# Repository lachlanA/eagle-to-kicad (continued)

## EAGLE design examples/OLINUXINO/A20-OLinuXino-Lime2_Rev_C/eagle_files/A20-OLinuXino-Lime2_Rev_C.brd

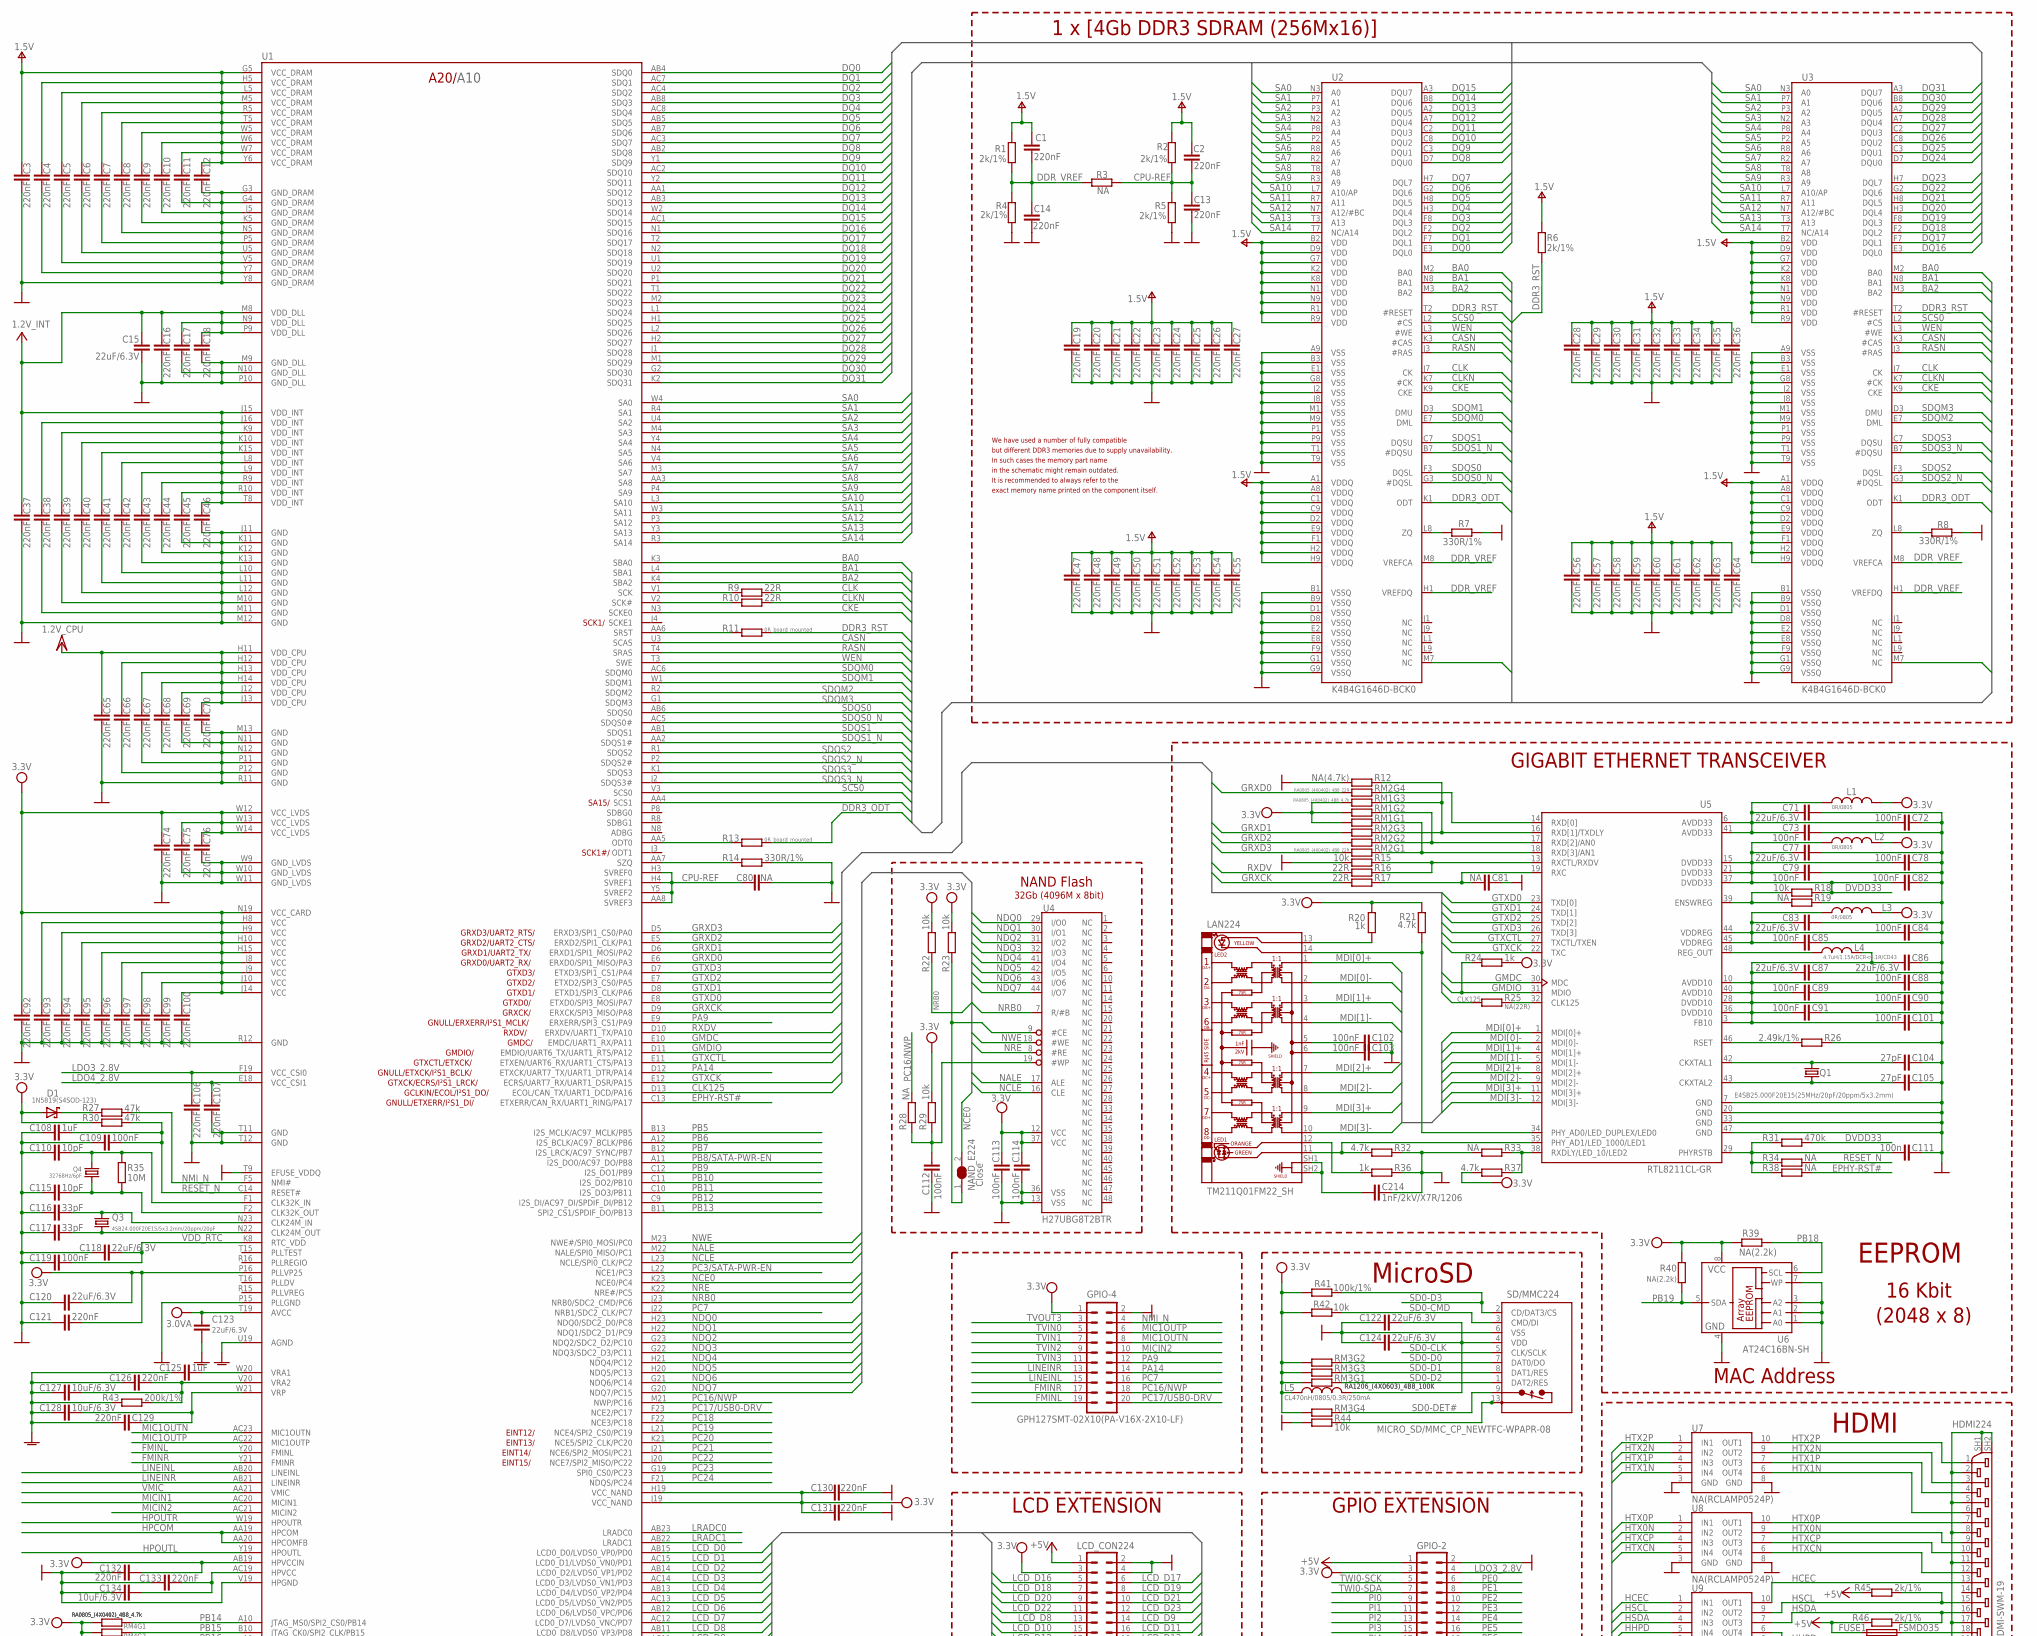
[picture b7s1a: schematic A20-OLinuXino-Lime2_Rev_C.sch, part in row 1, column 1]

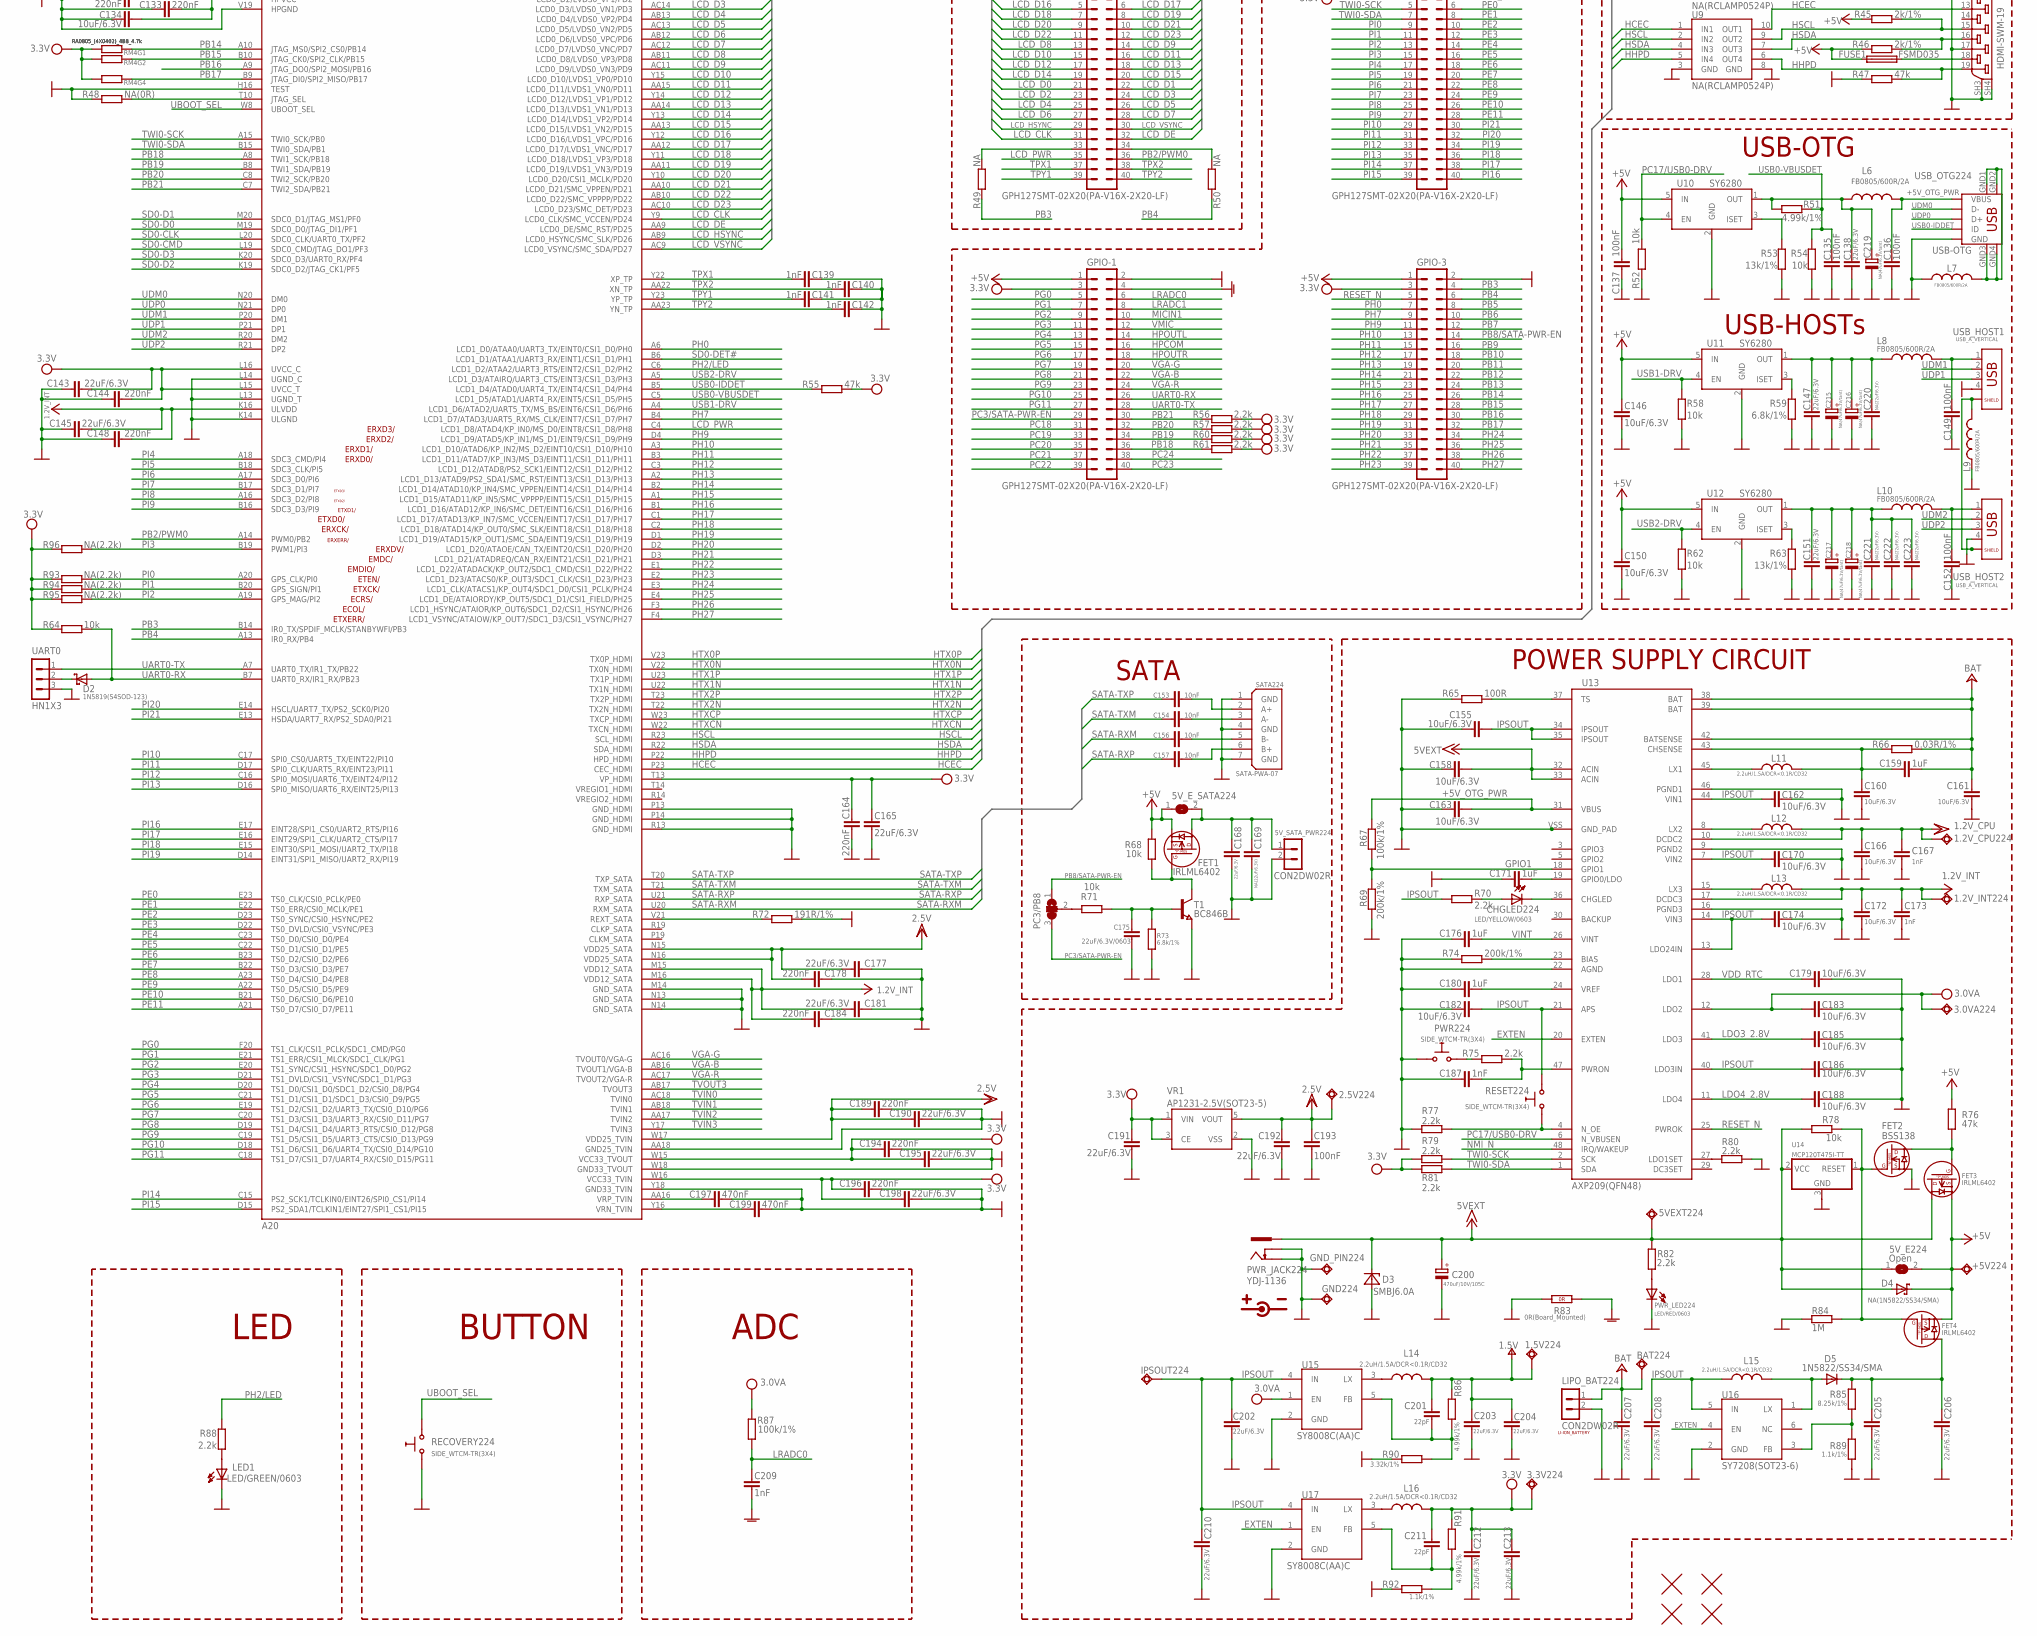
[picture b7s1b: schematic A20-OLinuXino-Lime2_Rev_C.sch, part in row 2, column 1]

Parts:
1.2V_CPU224, 1.2V_INT224, 1.5V224, 2.5V224, 3.0VA224, 3.3V224, 5VEXT224: TESTPADTESTPAD_40-ROUND; TESTPAD_40-ROUND
5V_E224: Open; SJ_1_SMALLER
5V_E_SATA224: SJSJ_SMALLER; SJ_1_SMALLER
5V_SATA_PWR224: CON2DW02R; DW02R
+5V224: TESTPADTESTPAD_40-ROUND; TESTPAD_40-ROUND
BAT224: TESTPADTESTPAD_40-ROUND; TESTPAD_40-ROUND
C1, C2, C3, C4, C5, C6, C7, C8, C9, C10, C11, C12, C13, C14, C16, C17, C18, C19, C20, C21, C22, C23, C24, C25, C26, C27, C28, C29, C30, C31, C32, C33, C34, C35, C36, C37, C38, C39, C40, C41, C42, C43, C44, C45, C46, C47, C48, C49, C50, C51, C52, C53, C54, C55, C56, C57, C58, C59, C60, C61, C62, C63, C64, C65, C66, C67, C68, C69, C70, C74, C75, C76, C92, C93, C94, C95, C96, C97, C98, C99, C100, C106, C107, C121, C126, C129, C130, C131, C132, C133, C144, C148, C164, C178, C184, C189, C194, C196: 220nF; C0402_TI
C15, C71, C77, C83, C86, C87, C118, C120, C122, C123, C124, C138, C143, C145, C147, C151, C165, C168, C177, C181, C190, C191, C192, C195, C198, C202, C203, C204, C205, C206, C207, C208, C210, C212, C213: 22uF/6.3V; C0603_DWS
C72, C73, C78, C79, C82, C84, C85, C88, C89, C90, C91, C101, C102, C103, C109, C112, C113, C114, C119, C135, C136, C137, C149, C152, C193: 100nF; C0402_TI
C80, C81: NA; C0402_TI
C104, C105: 27pF; C0603_DWS
C108, C125, C159, C171, C176, C180: 1uF; C0603_DWS
C110, C115: 10pF; C0402_TI
C111: 100n; C0402_TI
C116, C117: 33pF; C0603_DWS
C127, C128, C134, C146, C150, C155, C158, C160, C161, C162, C163, C166, C170, C172, C174, C179, C182, C183, C185, C186, C188: 10uF/6.3V; C0603_DWS
C139, C140, C141, C142, C167, C173, C187, C209: 1nF; C0402_TI
C153, C154, C156, C157: 10nF; C0402_TI
C169, C220, C221, C222, C223: NA(22uF/6.3V); C0603_DWS
C175: 22uF/6.3V/0603; C0603_DWS
C197, C199: 470nF; C0603_DWS
C200: 470uF/10V/105C; E2,5-6,3
C201, C211: 22pF; C0603_DWS
C214: 1nF/2kV/X7R/1206; C1206_5MILS_WS_ISO
C215, C216, C217, C218, C219: NA(47uF/6.3V/tant); CT3528_MIL
CHGLED224: LED/YELLOW/0603; LED-0603
D1, D2: 1N5819(S4SOD-123); SOD-123
D3: SMBJ6.0A; DO214AA
D4: NA(1N5822/SS34/SMA); MLL-41
D5: 1N5822/SS34/SMA; MELF-MLL41
FET1, FET3, FET4: IRLML6402; SOT23
FET2: BSS138; SOT23
FUSE1: FSMD035; 1206
GND224: TESTPADTESTPAD_40-ROUND; TESTPAD_40-ROUND
GND_PIN224: TESTPAD3; TEST_PAD40/70/SQUARE
GPIO-1, GPIO-2, GPIO-3: GPH127SMT-02X20(PA-V16X-2X20-LF)
GPIO-4: GPH127SMT-02X10(PA-V16X-2X10-LF)
HDMI224: HDMI-SWM-19
IPSOUT224: TESTPADTESTPAD_40-ROUND; TESTPAD_40-ROUND
L1, L2, L3: 0R/0805; L0805_5MIL_DWS
L4: 4.7uH/1.15A/DCR<0.1R/CD43; CD42(43)
L5: CL470nH/0805/0.3R/250mA; L0805_5MIL_DWS
L6, L7, L8, L9, L10: FB0805/600R/2A; L0805_5MIL_DWS
L11, L12, L13, L14, L15, L16: 2.2uH/1.5A/DCR<0.1R/CD32; CD32
LAN224: TM211Q01FM22_SH
LCD_CON224: GPH127SMT-02X20(PA-V16X-2X20-LF)
LED1: LED/GREEN/0603; LED-0603
LIPO_BAT224: CON2DW02R; DW02R
NAND_E224: Close; SJ_1_SMALLER_CLOSE_10MILS
PC3/PB8: SJ2W5; SJ_2_SMALL_23_TIED
PWR224: SIDE_WTCM-TR(3X4); SW_TAKT3X4
PWR_JACK224: YDJ-1136; PWR_JACK_UNI_MILLING
PWR_LED224: LED/RED/0603; LED-0603
Q1: E4SB25.000F20E15(25MHz/20pF/20ppm/5x3.2mm); HCX-4S
Q3: 4SB24.000F20E15/5x3.2mm/20ppm/20pF; HCX-4S
Q4: 32768Hz/6pF; MC-306
R1, R2, R4, R5, R6, R45, R46: 2k/1%; R0402_TI
R3, R19, R28, R33, R34, R38: NA; R0402_TI
R7, R8, R14: 330R/1%; R0603_5MIL_DWS
R9, R10, R16, R17: 22R; R0402_TI
R11, R13: 0R_board_mounted; R0402_TI_0R
R12: NA(4.7k); R0402_TI
R15, R18, R22, R23, R29, R42, R44, R52, R54, R58, R62, R64, R68, R71, R78: 10k; R0402_TI
R20, R24, R36: 1k; R0402_TI
R21, R32, R37: 4.7k; R0402_TI
R25: NA(22R); R0402_TI
R26: 2.49k/1%; R0603_5MIL_DWS
R27, R30, R47, R55, R76: 47k; R0402_TI
R31: 470k; R0402_TI
R35: 10M; R0402_TI
R39, R40, R93, R94, R95, R96: NA(2.2k); R0402_TI
R41, R67, R87: 100k/1%; R0603_5MIL_DWS
R43, R69, R74: 200k/1%; R0603_5MIL_DWS
R48: NA(0R); R0603_5MIL_DWS
R49, R50: NA; R0603_5MIL_DWS
R51, R86, R91: 4.99k/1%; R0603_5MIL_DWS
R53, R63: 13k/1%; R0603_5MIL_DWS
R56, R57, R60, R61, R70, R75, R77, R79, R80, R81, R82, R88: 2.2k; R0402_TI
R59, R73: 6.8k/1%; R0603_5MIL_DWS
R65: 100R; R0603_5MIL_DWS
R66: 0.03R/1%; R1206_5MIL_WS
R72: 191R/1%; R0603_5MIL_DWS
R83: 0R(Board_Mounted); 0603_0R
R84: 1M; R0402_TI
R85: 8.25k/1%; R0603_5MIL_DWS
R89, R92: 1.1k/1%; R0603_5MIL_DWS
R90: 3.32k/1%; R0603_5MIL_DWS
RECOVERY224: SIDE_WTCM-TR(3X4); SW_TAKT3X4
RESET224: SIDE_WTCM-TR(3X4); SW_TAKT3X4
RM1, RM4: RA0805_(4X0402)_4B8_4.7k; R_MATRIX_4_0402_25X625
RM2: RA0805_(4X0402)_4B8_22R; R_MATRIX_4_0402_25X625
RM3: RA1206_(4X0603)_4B8_100K; R_MATRIX_4
SATA224: SATA-PWA-07
SD/MMC224: MICRO_SD/MMC_CP_NEWTFC-WPAPR-08; TFC-WPAPR-08
T1: BC846B; SOT23
U1: A20; TFBGA441
U2, U3: K4B4G1646D-BCK0; FBGA96_SK
U4: H27UBG8T2BTR; TSOP48
U5: RTL8211CL-GR; LQFP48
U6: AT24C16BN-SH; SO-08MN
U7, U8, U9: NA(RCLAMP0524P); SLP2510P8
U10, U11, U12: SY6280; SOT23-5
U13: AXP209(QFN48); QFN48
U14: MCP120T475I-TT; SOT23
U15, U17: SY8008C(AA)C; SOT23-5
U16: SY7208(SOT23-6); SOT23-6
U18, U19, U20, U21: FIDUCIAL; FIDUCIAL-1X3
UART0: HN1X3
USB_HOST1, USB_HOST2: USB_A_VERTICAL; USB_A_VERTICAL_PTH
USB_OTG224: USB-OTG; USB_MINI_9PIN
VR1: AP1231-2.5V(SOT23-5); SOT-23-5

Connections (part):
5VEXT: 5VEXT224.1, 5V_E224.1, C158.2, C200.+, D3.C, D4.A, FET3.3 (D), PWR_JACK224.+, R78.1, R82.1, U13.32 (ACIN), U13.33 (ACIN), U14.2 (VCC)
+5V: 5V_E224.2, 5V_E_SATA224.1, +5V224.1, C137.1, C146.1, C150.1, D4.K (C), FET1.2 (S), FET3.2 (S), FET4.2 (S), FUSE1.1, GPIO-1.1, GPIO-2.1, GPIO-3.1, LCD_CON224.1, R45.2, R46.2, R68.1, R76.2, U10.5 (IN), U11.5 (IN), U12.5 (IN)
+5V_OTG_PWR: C136.1, C163.2, L6.1, R67.1, U13.31 (VBUS), USB_OTG224.VBUS
+24V: BAT224.1, C159.2, C161.1, C207.2, LIPO_BAT224.1, R66.2, U13.38 (BAT), U13.39 (BAT), U13.42 (BATSENSE)
AVDD1: C71.2, C72.2, C73.2, L1.2, U5.6 (AVDD33), U5.41 (AVDD33)
AVDD/DVDD(1.05V): C86.2, C87.2, C88.2, C89.2, C90.2, C91.2, C101.2, L4.2, U5.3 (FB10), U5.10 (AVDD10), U5.28 (DVDD10), U5.36 (DVDD10), U5.40 (AVDD10)
BA0: U1.K3 (SBA0), U2.M2 (BA0), U3.M2 (BA0)
BA1: U1.L4 (SBA1), U2.N8 (BA1), U3.N8 (BA1)
BA2: U1.K4 (SBA2), U2.M3 (BA2), U3.M3 (BA2)
CASN: U1.U3 (SCAS), U2.K3 (#CAS), U3.K3 (#CAS)
CKE: U1.N3 (SCKE0), U2.K9 (CKE), U3.K9 (CKE)
CLK: R9.1, U2.J7 (CK), U3.J7 (CK)
CLK125: R25.1, U1.D13 (ECOL/CAN_TX/UART1_DCD/PA16)
CLKN: R10.1, U2.K7 (#CK), U3.K7 (#CK)
CPU-REF: C2.2, C13.2, C80.2, R2.1, R3.2, R5.2, U1.AA8 (SVREF3), U1.H3 (SVREF0), U1.H4 (SVREF1), U1.Y5 (SVREF2)
DDR3_ODT: R13.1, U2.K1 (ODT), U3.K1 (ODT)
DDR3_RST: R6.1, R11.1, U2.T2 (#RESET), U3.T2 (#RESET)
DDR_VREF: C1.2, C14.2, R1.1, R3.1, R4.2, U2.H1 (VREFDQ), U2.M8 (VREFCA), U3.H1 (VREFDQ), U3.M8 (VREFCA)
DQ0: U1.AB4 (SDQ0), U2.E3 (DQL0)
DQ1: U1.AC7 (SDQ1), U2.F7 (DQL1)
DQ2: U1.AC4 (SDQ2), U2.F2 (DQL2)
DQ3: U1.AB8 (SDQ3), U2.F8 (DQL3)
DQ4: U1.AC8 (SDQ4), U2.H3 (DQL4)
DQ5: U1.AB5 (SDQ5), U2.H8 (DQL5)
DQ6: U1.AB7 (SDQ6), U2.G2 (DQL6)
DQ7: U1.AC3 (SDQ7), U2.H7 (DQL7)
DQ8: U1.AB2 (SDQ8), U2.D7 (DQU0)
DQ9: U1.Y1 (SDQ9), U2.C3 (DQU1)
DQ10: U1.AC2 (SDQ10), U2.C8 (DQU2)
DQ11: U1.Y2 (SDQ11), U2.C2 (DQU3)
DQ12: U1.AA1 (SDQ12), U2.A7 (DQU4)
DQ13: U1.AB3 (SDQ13), U2.A2 (DQU5)
DQ14: U1.W2 (SDQ14), U2.B8 (DQU6)
DQ15: U1.AC1 (SDQ15), U2.A3 (DQU7)
DQ16: U1.N1 (SDQ16), U3.E3 (DQL0)
DQ17: U1.T2 (SDQ17), U3.F7 (DQL1)
DQ18: U1.N2 (SDQ18), U3.F2 (DQL2)
DQ19: U1.U1 (SDQ19), U3.F8 (DQL3)
DQ20: U1.U2 (SDQ20), U3.H3 (DQL4)
DQ21: U1.P1 (SDQ21), U3.H8 (DQL5)
DQ22: U1.T1 (SDQ22), U3.G2 (DQL6)
DQ23: U1.M2 (SDQ23), U3.H7 (DQL7)
DQ24: U1.L1 (SDQ24), U3.D7 (DQU0)
DQ25: U1.H1 (SDQ25), U3.C3 (DQU1)
DQ26: U1.L2 (SDQ26), U3.C8 (DQU2)
DQ27: U1.H2 (SDQ27), U3.C2 (DQU3)
DQ28: U1.J1 (SDQ28), U3.A7 (DQU4)
DQ29: U1.M1 (SDQ29), U3.A2 (DQU5)
DQ30: U1.G2 (SDQ30), U3.B8 (DQU6)
DQ31: U1.K2 (SDQ31), U3.A3 (DQU7)
DVDD33: C77.2, C78.2, C79.2, C82.2, L2.2, R18.1, R31.1, U5.15 (DVDD33), U5.21 (DVDD33), U5.37 (DVDD33)
EPHY-RST#: R38.1, U1.C13 (ETXERR/CAN_RX/UART1_RING/PA17)
EXTEN: U13.20 (EXTEN), U16.4 (EN), U17.1 (EN)
FMINL: GPIO-4.19, U1.Y20 (FMINL)
FMINR: GPIO-4.17, U1.Y21 (FMINR)
GMDC: U1.E10 (EMDC/UART1_RX/PA11), U5.30 (MDC)
GMDIO: R24.1, U1.D11 (EMDIO/UART6_TX/UART1_RTS/PA12), U5.31 (MDIO)
GND: 5V_SATA_PWR224.2, C3.1, C4.1, C5.1, C6.1, C7.1, C8.1, C9.1, C10.1, C11.1, C12.1, C13.1, C14.1, C15.1, C16.1, C17.1, C18.1, C19.1, C20.1, C21.1, C22.1, C23.1, C24.1, C25.1, C26.1, C27.1, C28.1, C29.1, C30.1, C31.1, C32.1, C33.1, C34.1, C35.1, C36.1, C37.1, C38.1, C39.1, C40.1, C41.1, C42.1, C43.1, C44.1, C45.1, C46.1, C47.1, C48.1, C49.1, C50.1, C51.1, C52.1, C53.1, C54.1, C55.1, C56.1, C57.1, C58.1, C59.1, C60.1, C61.1, C62.1, C63.1, C64.1, C65.1, C66.1, C67.1, C68.1, C69.1, C70.1, C71.1, C72.1, C73.1, C74.1, C75.1, C76.1, C77.1, C78.1, C79.1, C80.1, C81.2, C82.1, C83.1, C84.1, C85.1, C86.1, C87.1, C88.1, C89.1, C90.1, C91.1, C92.1, C93.1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
GNDA: C123.1, C125.1, C126.1, C127.1, C128.1, C129.1, C209.2, GPIO-1.4, R43.2, R83.2 (1.2), U1.U19 (AGND)
GPIO1: R67.2, R69.1, U13.18 (GPIO1)
GRXCK: R17.2, U1.D9 (ERXCK/SPI3_MISO/PA8)
GRXD0: RM2.4.2 (2), U1.E6 (ERXD0/SPI1_MISO/PA3)
GRXD1: RM2.3.2 (2), U1.D6 (ERXD1/SPI1_MOSI/PA2)
GRXD2: RM2.2.2 (2), U1.E5 (ERXD2/SPI1_CLK/PA1)
GRXD3: RM2.1.2 (2), U1.D5 (ERXD3/SPI1_CS0/PA0)
GTXCK: U1.E12 (ECRS/UART7_RX/UART1_DSR/PA15), U5.22 (TXC)
GTXCTL: U1.E11 (ETXEN/UART6_RX/UART1_CTS/PA13), U5.27 (TXCTL/TXEN)
GTXD0: U1.E8 (ETXD0/SPI3_MOSI/PA7), U5.23 (TXD[0])
GTXD1: U1.D8 (ETXD1/SPI3_CLK/PA6), U5.24 (TXD[1])
GTXD2: U1.E7 (ETXD2/SPI3_CS0/PA5), U5.25 (TXD[2])
GTXD3: U1.D7 (ETXD3/SPI1_CS1/PA4), U5.26 (TXD[3])
HCEC: HDMI224.13, U1.P23 (CEC_HDMI), U9.1 (IN1), U9.10 (OUT1)
HDMI_5V_SOURCE: FUSE1.2, HDMI224.18
HHPD: HDMI224.19, R47.1, U1.P22 (HPD_HDMI), U9.5 (IN4), U9.6 (OUT4)
HPCOM: GPIO-1.16, U1.AA19 (HPCOM), U1.AA20 (HPCOMFB)
HPOUTL: GPIO-1.14, U1.Y19 (HPOUTL)
HPOUTR: GPIO-1.18, U1.W19 (HPOUTR)
HSCL: HDMI224.15, R45.1, U1.R23 (SCL_HDMI), U9.2 (IN2), U9.9 (OUT2)
HSDA: HDMI224.16, R46.1, U1.R22 (SDA_HDMI), U9.4 (IN3), U9.7 (OUT3)
HTX0N: HDMI224.9, U1.V22 (TX0N_HDMI), U8.2 (IN2), U8.9 (OUT2)
HTX0P: HDMI224.7, U1.V23 (TX0P_HDMI), U8.1 (IN1), U8.10 (OUT1)
HTX1N: HDMI224.6, U1.U22 (TX1N_HDMI), U7.5 (IN4), U7.6 (OUT4)
HTX1P: HDMI224.4, U1.U23 (TX1P_HDMI), U7.4 (IN3), U7.7 (OUT3)
HTX2N: HDMI224.3, U1.T22 (TX2N_HDMI), U7.2 (IN2), U7.9 (OUT2)
HTX2P: HDMI224.1, U1.T23 (TX2P_HDMI), U7.1 (IN1), U7.10 (OUT1)
HTXCN: HDMI224.12, U1.W22 (TXCN_HDMI), U8.5 (IN4), U8.6 (OUT4)
HTXCP: HDMI224.10, U1.W23 (TXCP_HDMI), U8.4 (IN3), U8.7 (OUT3)
IPSOUT: C155.2, C162.1, C170.1, C174.1, C182.2, C186.1, C202.1, C208.2, C210.1, IPSOUT224.1, L15.1, R70.1, RESET224.1_1 (1), U13.7 (VIN2), U13.13 (LDO24IN), U13.14 (VIN3), U13.21 (APS), U13.34 (IPSOUT), U13.35 (IPSOUT), U13.40 (LDO3IN), U13.44 (VIN1), U15.4 (IN), U16.5 (IN), U17.4 (IN)
LAN_SH: C214.2, LAN224.SH1, LAN224.SH2
LCD_CLK: LCD_CON224.31, U1.Y9 (LCD0_CLK/SMC_VCCEN/PD24)
LCD_D0: LCD_CON224.21, U1.AB15 (LCD0_D0/LVDS0_VP0/PD0)
LCD_D1: LCD_CON224.22, U1.AC15 (LCD0_D1/LVDS0_VN0/PD1)
LCD_D2: LCD_CON224.23, U1.AB14 (LCD0_D2/LVDS0_VP1/PD2)
LCD_D3: LCD_CON224.24, U1.AC14 (LCD0_D3/LVDS0_VN1/PD3)
LCD_D4: LCD_CON224.25, U1.AB13 (LCD0_D4/LVDS0_VP2/PD4)
LCD_D5: LCD_CON224.26, U1.AC13 (LCD0_D5/LVDS0_VN2/PD5)
LCD_D6: LCD_CON224.27, U1.AB12 (LCD0_D6/LVDS0_VPC/PD6)
LCD_D7: LCD_CON224.28, U1.AC12 (LCD0_D7/LVDS0_VNC/PD7)
LCD_D8: LCD_CON224.13, U1.AB11 (LCD0_D8/LVDS0_VP3/PD8)
LCD_D9: LCD_CON224.14, U1.AC11 (LCD0_D9/LVDS0_VN3/PD9)
LCD_D10: LCD_CON224.15, U1.Y15 (LCD0_D10/LVDS1_VP0/PD10)
LCD_D11: LCD_CON224.16, U1.AA15 (LCD0_D11/LVDS1_VN0/PD11)
LCD_D12: LCD_CON224.17, U1.Y14 (LCD0_D12/LVDS1_VP1/PD12)
LCD_D13: LCD_CON224.18, U1.AA14 (LCD0_D13/LVDS1_VN1/PD13)
LCD_D14: LCD_CON224.19, U1.Y13 (LCD0_D14/LVDS1_VP2/PD14)
LCD_D15: LCD_CON224.20, U1.AA13 (LCD0_D15/LVDS1_VN2/PD15)
LCD_D16: LCD_CON224.5, U1.Y12 (LCD0_D16/LVDS1_VPC/PD16)
LCD_D17: LCD_CON224.6, U1.AA12 (LCD0_D17/LVDS1_VNC/PD17)
LCD_D18: LCD_CON224.7, U1.Y11 (LCD0_D18/LVDS1_VP3/PD18)
LCD_D19: LCD_CON224.8, U1.AA11 (LCD0_D19/LVDS1_VN3/PD19)
LCD_D20: LCD_CON224.9, U1.Y10 (LCD0_D20/CSI1_MCLK/PD20)
LCD_D21: LCD_CON224.10, U1.AA10 (LCD0_D21/SMC_VPPEN/PD21)
LCD_D22: LCD_CON224.11, U1.AB10 (LCD0_D22/SMC_VPPPP/PD22)
LCD_D23: LCD_CON224.12, U1.AC10 (LCD0_D23/SMC_DET/PD23)
LCD_DE: LCD_CON224.32, U1.AA9 (LCD0_DE/SMC_RST/PD25)
LCD_HSYNC: LCD_CON224.29, U1.AB9 (LCD0_HSYNC/SMC_SLK/PD26)
LCD_PWR: LCD_CON224.35, U1.C4 (LCD1_D8/ATAD4/KP_IN0/MS_D0/EINT8/CSI1_D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)
LCD_VSYNC: LCD_CON224.30, U1.AC9 (LCD0_VSYNC/SMC_SDA/PD27)
LDO3_2.8V: C106.2, C185.1, GPIO-2.4, U1.F19 (VCC_CSI0), U13.41 (LDO3)
LDO4_2.8V: C107.2, C188.1, U1.E18 (VCC_CSI1), U13.11 (LDO4)
LINEINL: GPIO-4.15, U1.AB20 (LINEINL)
LINEINR: GPIO-4.13, U1.AB21 (LINEINR)
LRADC0: C209.1, GPIO-1.6, R87.2, U1.AB23 (LRADC0)
LRADC1: GPIO-1.8, U1.AB22 (LRADC1)
MDI[0]+: LAN224.1, U5.1 (MDI[0]+)
MDI[0]-: LAN224.2, U5.2 (MDI[0]-)
MDI[1]+: LAN224.3, U5.4 (MDI[1]+)
MDI[1]-: LAN224.4, U5.5 (MDI[1]-)
MDI[2]+: LAN224.7, U5.8 (MDI[2]+)
MDI[2]-: LAN224.8, U5.9 (MDI[2]-)
MDI[3]+: LAN224.9, U5.11 (MDI[3]+)
MDI[3]-: LAN224.10, U5.12 (MDI[3]-)
MIC1OUTN: GPIO-4.8, U1.AC23 (MIC1OUTN)
MIC1OUTP: GPIO-4.6, U1.AC22 (MIC1OUTP)
MICIN1: GPIO-1.10, U1.AC20 (MICIN1)
MICIN2: GPIO-4.10, U1.AC21 (MICIN2)
unnamed: C133.2, C134.2, U1.AC19 (HPVCC)
unnamed: R14.2, U1.AA7 (SZQ)
unnamed: R7.2, U2.L8 (ZQ)
unnamed: CHGLED224.A, R70.2
unnamed: PC3/PB8.2, R71.2
unnamed: D2.C, UART0.2
unnamed: L14.1, U15.3 (LX)
unnamed: C171.2, U13.19 (GPIO0/LDO)
unnamed: D1.C, R27.2
unnamed: CHGLED224.C, U13.36 (CHGLED)
unnamed: R80.1, U13.27 (LDO1SET)
unnamed: C151.2, C217.+, C218.+, C221.2, C222.2, C223.2, L10.1, U12.1 (OUT)
unnamed: C110.2, Q4.1, R35.1, U1.F1 (CLK32K_IN)
unnamed: R8.2, U3.L8 (ZQ)
unnamed: L4.1, U5.48 (REG_OUT)
unnamed: C175.1, R71.1, R73.2, T1.1 (B)
unnamed: FET1.1 (G), R68.2, T1.3 (C)
unnamed: C201.2, R86.2, R90.1, U15.5 (FB)
unnamed: R26.2, U5.46 (RSET)
unnamed: FET2.3 (D), FET3.1 (G), R76.1
unnamed: C104.2, Q1.2, U5.42 (CKXTAL1)
unnamed: C205.1, C206.1, D5.1 (C), FET4.3 (D), R85.2
unnamed: 5V_E_SATA224.2, 5V_SATA_PWR224.1, C168.2, C169.2, FET1.3 (D)
unnamed: C105.2, Q1.1, U5.43 (CKXTAL2)
unnamed: C111.2, R31.2, R34.2, R38.2, U5.29 (PHYRSTB)
unnamed: C102.2, LAN224.5
unnamed: C103.2, LAN224.6
unnamed: R33.1, R37.1, U5.38 (RXDLY/LED_10/LED2)
unnamed: LAN224.12, R36.2
unnamed: LAN224.11, R32.2, U5.35 (PHY_AD1/LED_1000/LED1)
unnamed: FET2.1 (G), FET4.1 (G), R78.2, R84.2, U14.1 (RESET)
unnamed: R18.2, R19.2, U5.39 (ENSWREG)
unnamed: LAN224.13, R20.2
unnamed: C81.1, R17.1, U5.19 (RXC)
unnamed: R15.1, R16.1, U5.13 (RXCTL/RXDV)
unnamed: PWR224.1_1 (1), R75.1
unnamed: C197.2, U1.AA16 (VRP_TVIN)
unnamed: RM2.4.1 (1), U5.14 (RXD[0])
unnamed: R12.1, RM1.3.1 (1), RM2.3.1 (1), U5.16 (RXD[1]/TXDLY)
unnamed: RM1.2.1 (1), RM2.2.1 (1), U5.17 (RXD[2]/AN0)
unnamed: RM1.1.1 (1), RM2.1.1 (1), U5.18 (RXD[3]/AN1)
unnamed: LAN224.14, R21.1, U5.34 (PHY_AD0/LED_DUPLEX/LED0)
unnamed: R25.2, U5.32 (CLK125)
unnamed: R44.1, SD/MMC224.10 (PACK1), SD/MMC224.11 (PACK2), SD/MMC224.12 (PACK3), SD/MMC224.13 (PACK4)
unnamed: L16.1, U17.3 (LX)
unnamed: C211.2, R91.2, R92.1, U17.5 (FB)
unnamed: R53.2, U10.3 (ISET)
unnamed: C138.2, C219.+, L6.2, R51.2, U10.1 (OUT)
unnamed: R63.2, U12.3 (ISET)
unnamed: C153.2, SATA224.2 (A+)
unnamed: C152.1, L10.2, USB_HOST2.1
unnamed: C154.2, SATA224.3 (A-)
unnamed: C156.2, SATA224.5 (B-)
unnamed: C157.2, SATA224.6 (B+)
unnamed: C115.2, Q4.4 (2), R35.2, U1.F2 (CLK32K_OUT)
unnamed: R72.2, U1.V21 (REXT_SATA)
unnamed: R74.2, U13.23 (BIAS)
unnamed: C128.2, C129.2, U1.W21 (VRP)
unnamed: D5.2 (A), L15.2, U16.1 (LX)
unnamed: C112.2, R28.2, R29.2, U4.19 (#WP)
unnamed: R65.2, U13.37 (TS)
unnamed: R85.1, R89.1, U16.3 (FB)
unnamed: L11.1, U13.45 (LX1)
unnamed: C159.1, C160.1, L11.2, R66.1, U13.43 (CHSENSE)
unnamed: PWR_LED224.A, R82.2
unnamed: L12.1, U13.8 (LX2)
unnamed: L13.1, U13.15 (LX3)
unnamed: C180.2, U13.24 (VREF)
unnamed: C125.2, U1.W20 (VRA1)
unnamed: R59.2, U11.3 (ISET)
unnamed: C187.2, R75.2, U13.47 (PWRON)
unnamed: R77.2, RESET224.2_1 (0), U13.4 (N_OE)
unnamed: C126.2, C127.2, R43.1, U1.V20 (VRA2)
unnamed: R48.1, U1.T10 (JTAG_SEL)
unnamed: L9.2, USB_HOST1.P$3 (5), USB_HOST1.P$4 (6), USB_HOST2.P$3 (5), USB_HOST2.P$4 (6)
unnamed: C149.1, L8.2, USB_HOST1.1
unnamed: C147.2, C215.+, C216.+, C220.2, L8.1, U11.1 (OUT)
unnamed: C199.2, U1.Y16 (VRN_TVIN)
unnamed: LCD_CON224.33, R49.1
unnamed: LCD_CON224.34, R50.1
unnamed: LED1.A, R88.2
unnamed: NAND_E224.1, R23.2, U4.9 (#CE)
unnamed: L7.2, USB_OTG224.GND1, USB_OTG224.GND2, USB_OTG224.GND3, USB_OTG224.GND4
NALE: U1.M22 (NALE/SPI0_MISO/PC1), U4.17 (ALE)
NCE0: NAND_E224.2, U1.K23 (NCE0/PC4)
NCLE: U1.L23 (NCLE/SPI0_CLK/PC2), U4.16 (CLE)
NDQ0: U1.H23 (NDQ0/SDC2_D0/PC8), U4.29 (I/O0)
NDQ1: U1.H22 (NDQ1/SDC2_D1/PC9), U4.30 (I/O1)
NDQ2: U1.G23 (NDQ2/SDC2_D2/PC10), U4.31 (I/O2)
NDQ3: U1.G22 (NDQ3/SDC2_D3/PC11), U4.32 (I/O3)
NDQ4: U1.H21 (NDQ4/PC12), U4.41 (I/O4)
NDQ5: U1.H20 (NDQ5/PC13), U4.42 (I/O5)
NDQ6: U1.G21 (NDQ6/PC14), U4.43 (I/O6)
NDQ7: U1.G20 (NDQ7/PC15), U4.44 (I/O7)
NMI_N: GPIO-4.4, R27.1, U1.F5 (NMI#), U13.48 (IRQ/WAKEUP)
NRB0: R22.2, U1.J23 (NRB0/SDC2_CMD/PC6), U4.7 (R/#B)
NRE: U1.K22 (NRE#/PC5), U4.8 (#RE)
NWE: U1.M23 (NWE#/SPI0_MOSI/PC0), U4.18 (#WE)
ODT0: R13.2, U1.AA5 (ODT0)
PA9: GPIO-4.12, U1.E9 (ERXERR/SPI3_CS1/PA9)
PA14: GPIO-4.14, U1.D12 (ETXCK/UART7_TX/UART1_DTR/PA14)
PB2/PWM0: LCD_CON224.36, U1.A14 (PWM0/PB2)
PB3: GPIO-3.4, R49.2, U1.B14 (IR0_TX/SPDIF_MCLK/STANBYWFI/PB3)
PB4: GPIO-3.6, R50.2, U1.A13 (IR0_RX/PB4)
PB5: GPIO-3.8, U1.B13 (I2S_MCLK/AC97_MCLK/PB5)
PB6: GPIO-3.10, U1.A12 (I2S_BCLK/AC97_BCLK/PB6)
PB7: GPIO-3.12, U1.B12 (I2S_LRCK/AC97_SYNC/PB7)
PB8/SATA-PWR-EN: GPIO-3.14, PC3/PB8.1, U1.A11 (I2S_DO0/AC97_DO/PB8)
PB9: GPIO-3.16, U1.C12 (I2S_DO1/PB9)
PB10: GPIO-3.18, U1.C11 (I2S_DO2/PB10)
PB11: GPIO-3.20, U1.C10 (I2S_DO3/PB11)
PB12: GPIO-3.22, U1.C9 (I2S_DI/AC97_DI/SPDIF_DI/PB12)
PB13: GPIO-3.24, U1.B11 (SPI2_CS1/SPDIF_DO/PB13)
PB14: GPIO-3.26, RM4.1.1 (1), U1.A10 (JTAG_MS0/SPI2_CS0/PB14)
PB15: GPIO-3.28, RM4.2.1 (1), U1.B10 (JTAG_CK0/SPI2_CLK/PB15)
PB16: GPIO-3.30, U1.A9 (JTAG_DO0/SPI2_MOSI/PB16)
PB17: GPIO-3.32, RM4.4.1 (1), U1.B9 (JTAG_DI0/SPI2_MISO/PB17)
PB18: GPIO-1.36, R39.2, R61.1, U1.A8 (TWI1_SCK/PB18), U6.6 (SCL)
PB19: GPIO-1.34, R40.1, R60.1, U1.B8 (TWI1_SDA/PB19), U6.5 (SDA)
PB20: GPIO-1.32, R57.1, U1.C8 (TWI2_SCK/PB20)
PB21: GPIO-1.30, R56.1, U1.C7 (TWI2_SDA/PB21)
PC3/SATA-PWR-EN: GPIO-1.29, PC3/PB8.3, U1.L22 (NCE1/PC3)
PC7: GPIO-4.16, U1.J22 (NRB1/SDC2_CLK/PC7)
PC16/NWP: GPIO-4.18, R28.1, U1.M21 (NWP/PC16)
PC17/USB0-DRV: GPIO-4.20, R52.2, U1.F23 (NCE2/PC17), U10.4 (EN), U13.6 (N_VBUSEN)
PC18: GPIO-1.31, U1.F22 (NCE3/PC18)
PC19: GPIO-1.33, U1.L21 (NCE4/SPI2_CS0/PC19)
PC20: GPIO-1.35, U1.K21 (NCE5/SPI2_CLK/PC20)
PC21: GPIO-1.37, U1.J21 (NCE6/SPI2_MOSI/PC21)
PC22: GPIO-1.39, U1.J20 (NCE7/SPI2_MISO/PC22)
PC23: GPIO-1.40, U1.G19 (SPI0_CS0/PC23)
PC24: GPIO-1.38, U1.F21 (NDQS/PC24)
PE0: GPIO-2.6, U1.E23 (TS0_CLK/CSI0_PCLK/PE0)
PE1: GPIO-2.8, U1.E22 (TS0_ERR/CSI0_MCLK/PE1)
PE2: GPIO-2.10, U1.D23 (TS0_SYNC/CSI0_HSYNC/PE2)
PE3: GPIO-2.12, U1.D22 (TS0_DVLD/CSI0_VSYNC/PE3)
PE4: GPIO-2.14, U1.C23 (TS0_D0/CSI0_D0/PE4)
PE5: GPIO-2.16, U1.C22 (TS0_D1/CSI0_D1/PE5)
PE6: GPIO-2.18, U1.B23 (TS0_D2/CSI0_D2/PE6)
PE7: GPIO-2.20, U1.B22 (TS0_D3/CSI0_D3/PE7)
PE8: GPIO-2.22, U1.A23 (TS0_D4/CSI0_D4/PE8)
PE9: GPIO-2.24, U1.A22 (TS0_D5/CSI0_D5/PE9)
PE10: GPIO-2.26, U1.B21 (TS0_D6/CSI0_D6/PE10)
PE11: GPIO-2.28, U1.A21 (TS0_D7/CSI0_D7/PE11)
PG0: GPIO-1.5, U1.F20 (TS1_CLK/CSI1_PCLK/SDC1_CMD/PG0)
PG1: GPIO-1.7, U1.E21 (TS1_ERR/CSI1_MLCK/SDC1_CLK/PG1)
PG2: GPIO-1.9, U1.E20 (TS1_SYNC/CSI1_HSYNC/SDC1_D0/PG2)
PG3: GPIO-1.11, U1.D21 (TS1_DVLD/CSI1_VSYNC/SDC1_D1/PG3)
PG4: GPIO-1.13, U1.D20 (TS1_D0/CSI1_D0/SDC1_D2/CSI0_D8/PG4)
PG5: GPIO-1.15, U1.C21 (TS1_D1/CSI1_D1/SDC1_D3/CSI0_D9/PG5)
PG6: GPIO-1.17, U1.E19 (TS1_D2/CSI1_D2/UART3_TX/CSI0_D10/PG6)
PG7: GPIO-1.19, U1.C20 (TS1_D3/CSI1_D3/UART3_RX/CSI0_D11/PG7)
PG8: GPIO-1.21, U1.D19 (TS1_D4/CSI1_D4/UART3_RTS/CSI0_D12/PG8)
PG9: GPIO-1.23, U1.C19 (TS1_D5/CSI1_D5/UART3_CTS/CSI0_D13/PG9)
PG10: GPIO-1.25, U1.D18 (TS1_D6/CSI1_D6/UART4_TX/CSI0_D14/PG10)
PG11: GPIO-1.27, U1.C18 (TS1_D7/CSI1_D7/UART4_RX/CSI0_D15/PG11)
PH0: GPIO-3.7, U1.A6 (LCD1_D0/ATAA0/UART3_TX/EINT0/CSI1_D0/PH0)
PH2/LED: R88.1, U1.C6 (LCD1_D2/ATAA2/UART3_RTS/EINT2/CSI1_D2/P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)
PH7: GPIO-3.9, U1.B4 (LCD1_D7/ATAD3/UART5_RX/MS_CLK/EINT7/CSI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)
PH9: GPIO-3.11, U1.D4 (LCD1_D9/ATAD5/KP_IN1/MS_D1/EINT9/CSI1_D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)
PH10: GPIO-3.13, U1.A3 (LCD1_D10/ATAD6/KP_IN2/MS_D2/EINT10/CSI1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)
PH11: GPIO-3.15, U1.B3 (LCD1_D11/ATAD7/KP_IN3/MS_D3/EINT11/CSI1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)
PH12: GPIO-3.17, U1.C3 (LCD1_D12/ATAD8/PS2_SCK1/EINT12/CSI1_D12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)
PH13: GPIO-3.19, U1.A2 (LCD1_D13/ATAD9/PS2_SDA1/SMC_RST/EINT13/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)
PH14: GPIO-3.21, U1.B2 (LCD1_D14/ATAD10/KP_IN4/SMC_VPPEN/EINT14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)
PH15: GPIO-3.23, U1.A1 (LCD1_D15/ATAD11/KP_IN5/SMC_VPPPP/EINT15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)
PH16: GPIO-3.25, U1.B1 (LCD1_D16/ATAD12/KP_IN6/SMC_DET/EINT16/C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)
PH17: GPIO-3.27, U1.C1 (LCD1_D17/ATAD13/KP_IN7/SMC_VCCEN/EINT17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)
PH18: GPIO-3.29, U1.C2 (LCD1_D18/ATAD14/KP_OUT0/SMC_SLK/EINT18/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)
PH19: GPIO-3.31, U1.D1 (LCD1_D19/ATAD15/KP_OUT1/SMC_SDA/EINT19/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)
PH20: GPIO-3.33, U1.D2 (LCD1_D20/ATAOE/CAN_TX/EINT20/CSI1_D20/P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)
PH21: GPIO-3.35, U1.D3 (LCD1_D21/ATADREQ/CAN_RX/EINT21/CSI1_D21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)
PH22: GPIO-3.37, U1.E1 (LCD1_D22/ATADACK/KP_OUT2/SDC1_CMD/CSI1_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)
PH23: GPIO-3.39, U1.E2 (LCD1_D23/ATACS0/KP_OUT3/SDC1_CLK/CSI1_D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)
PH24: GPIO-3.34, U1.E3 (LCD1_CLK/ATACS1/KP_OUT4/SDC1_D0/CSI1_PC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)
PH25: GPIO-3.36, U1.E4 (LCD1_DE/ATAIORDY/KP_OUT5/SDC1_D1/CSI1_F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)
PH26: GPIO-3.38, U1.F3 (LCD1_HSYNC/ATAIOR/KP_OUT6/SDC1_D2/CSI1_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)
PH27: GPIO-3.40, U1.F4 (LCD1_VSYNC/ATAIOW/KP_OUT7/SDC1_D3/CSI1_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)
PI0: GPIO-2.9, R93.1, U1.A20 (GPS_CLK/PI0)
PI1: GPIO-2.11, R94.1, U1.B20 (GPS_SIGN/PI1)
PI2: GPIO-2.13, R95.1, U1.A19 (GPS_MAG/PI2)
PI3: GPIO-2.15, R96.1, U1.B19 (PWM1/PI3)
PI4: GPIO-2.17, U1.A18 (SDC3_CMD/PI4)
PI5: GPIO-2.19, U1.B18 (SDC3_CLK/PI5)
PI6: GPIO-2.21, U1.A17 (SDC3_D0/PI6)
PI7: GPIO-2.23, U1.B17 (SDC3_D1/PI7)
PI8: GPIO-2.25, U1.A16 (SDC3_D2/PI8)
PI9: GPIO-2.27, U1.B16 (SDC3_D3/PI9)
PI10: GPIO-2.29, U1.C17 (SPI0_CS0/UART5_TX/EINT22/PI10)
PI11: GPIO-2.31, U1.D17 (SPI0_CLK/UART5_RX/EINT23/PI11)
PI12: GPIO-2.33, U1.C16 (SPI0_MOSI/UART6_TX/EINT24/PI12)
PI13: GPIO-2.35, U1.D16 (SPI0_MISO/UART6_RX/EINT25/PI13)
PI14: GPIO-2.37, U1.C15 (PS2_SCK1/TCLKIN0/EINT26/SPI0_CS1/PI14)
PI15: GPIO-2.39, U1.D15 (PS2_SDA1/TCLKIN1/EINT27/SPI1_CS1/PI15)
PI16: GPIO-2.40, U1.E17 (EINT28/SPI1_CS0/UART2_RTS/PI16)
PI17: GPIO-2.38, U1.E16 (EINT29/SPI1_CLK/UART2_CTS/PI17)
PI18: GPIO-2.36, U1.E15 (EINT30/SPI1_MOSI/UART2_TX/PI18)
PI19: GPIO-2.34, U1.D14 (EINT31/SPI1_MISO/UART2_RX/PI19)
PI20: GPIO-2.32, U1.E14 (HSCL/UART7_TX/PS2_SCK0/PI20)
PI21: GPIO-2.30, U1.E13 (HSDA/UART7_RX/PS2_SDA0/PI21)
RASN: U1.T4 (SRAS), U2.J3 (#RAS), U3.J3 (#RAS)
RESET_N: C108.2, C109.2, GPIO-3.5, R30.1, R34.1, U1.C14 (RESET#), U13.25 (PWROK)
RXDV: R16.2, U1.D10 (ERXDV/UART1_TX/PA10)
SA0: U1.W4 (SA0), U2.N3 (A0), U3.N3 (A0)
SA1: U1.R4 (SA1), U2.P7 (A1), U3.P7 (A1)
SA2: U1.U4 (SA2), U2.P3 (A2), U3.P3 (A2)
SA3: U1.M4 (SA3), U2.N2 (A3), U3.N2 (A3)
SA4: U1.Y4 (SA4), U2.P8 (A4), U3.P8 (A4)
SA5: U1.N4 (SA5), U2.P2 (A5), U3.P2 (A5)
SA6: U1.V4 (SA6), U2.R8 (A6), U3.R8 (A6)
SA7: U1.M3 (SA7), U2.R2 (A7), U3.R2 (A7)
SA8: U1.AA3 (SA8), U2.T8 (A8), U3.T8 (A8)
SA9: U1.P4 (SA9), U2.R3 (A9), U3.R3 (A9)
SA10: U1.L3 (SA10), U2.L7 (A10/AP), U3.L7 (A10/AP)
SA11: U1.W3 (SA11), U2.R7 (A11), U3.R7 (A11)
SA12: U1.P3 (SA12), U2.N7 (A12/#BC), U3.N7 (A12/#BC)
SA13: U1.Y3 (SA13), U2.T3 (A13), U3.T3 (A13)
SA14: U1.R3 (SA14), U2.T7 (NC/A14), U3.T7 (NC/A14)
SA15: U1.AA4 (SCS1), U2.M7 (NC), U3.M7 (NC)
SATA-RXM: C156.1, U1.U20 (RXM_SATA)
SATA-RXP: C157.1, U1.U21 (RXP_SATA)
SATA-TXM: C154.1, U1.T21 (TXM_SATA)
SATA-TXP: C153.1, U1.T20 (TXP_SATA)
SCK: R9.2, U1.V1 (SCK)
SCK#: R10.2, U1.V2 (SCK#)
SCS0: U1.V3 (SCS0), U2.L2 (#CS), U3.L2 (#CS)
SD0-CLK: SD/MMC224.5 (CLK/SCLK), U1.L20 (SDC0_CLK/UART0_TX/PF2)
SD0-CMD: R42.1, SD/MMC224.3 (CMD/DI), U1.L19 (SDC0_CMD/JTAG_DO1/PF3)
SD0-D0: RM3.2.2 (2), SD/MMC224.7 (DAT0/DO), U1.M19 (SDC0_D0/JTAG_DI1/PF1)
SD0-D1: RM3.3.2 (2), SD/MMC224.8 (DAT1/RES), U1.M20 (SDC0_D1/JTAG_MS1/PF0)
SD0-D2: RM3.1.2 (2), SD/MMC224.1 (DAT2/RES), U1.K19 (SDC0_D2/JTAG_CK1/PF5)
SD0-D3: R41.1, SD/MMC224.2 (CD/DAT3/CS), U1.K20 (SDC0_D3/UART0_RX/PF4)
SD0-DET#: RM3.4.2 (2), SD/MMC224.9 (CP_E), U1.B6 (LCD1_D1/ATAA1/UART3_RX/EINT1/CSI1_D1/PH1)
SDQM0: U1.AC6 (SDQM0), U2.E7 (DML)
SDQM1: U1.W1 (SDQM1), U2.D3 (DMU)
SDQM2: U1.R2 (SDQM2), U3.E7 (DML)
SDQM3: U1.G1 (SDQM3), U3.D3 (DMU)
SDQS0: U1.AB6 (SDQS0), U2.F3 (DQSL)
SDQS0_N: U1.AC5 (SDQS0#), U2.G3 (#DQSL)
SDQS1: U1.AB1 (SDQS1), U2.C7 (DQSU)
SDQS1_N: U1.AA2 (SDQS1#), U2.B7 (#DQSU)
SDQS2: U1.R1 (SDQS2), U3.F3 (DQSL)
SDQS2_N: U1.P2 (SDQS2#), U3.G3 (#DQSL)
SDQS3: U1.K1 (SDQS3), U3.C7 (DQSU)
SDQS3_N: U1.J2 (SDQS3#), U3.B7 (#DQSU)
SD_VCC: C122.2, C124.2, L5.2, SD/MMC224.4 (VDD)
SRST: R11.2, U1.AA6 (SRST)
TPX1: C139.2, LCD_CON224.37, U1.Y22 (XP_TP)
TPX2: C140.2, LCD_CON224.38, U1.AA22 (XN_TP)
TPY1: C141.2, LCD_CON224.39, U1.Y23 (YP_TP)
TPY2: C142.2, LCD_CON224.40, U1.AA23 (YN_TP)
TVIN0: GPIO-4.5, U1.AC18 (TVIN0)
TVIN1: GPIO-4.7, U1.AB18 (TVIN1)
TVIN2: GPIO-4.9, U1.AA17 (TVIN2)
TVIN3: GPIO-4.11, U1.Y17 (TVIN3)
TVOUT3: GPIO-4.3, U1.AB17 (TVOUT3)
TWI0-SCK: GPIO-2.5, R79.1, U1.A15 (TWI0_SCK/PB0), U13.2 (SCK)
TWI0-SDA: GPIO-2.7, R81.1, U1.B15 (TWI0_SDA/PB1), U13.1 (SDA)
UART0-RX: D2.A, GPIO-1.26, R64.1, U1.B7 (UART0_RX/IR1_RX/PB23)
UART0-TX: GPIO-1.28, U1.A7 (UART0_TX/IR1_TX/PB22), UART0.1
UBOOT_SEL: RECOVERY224.2_1 (0), U1.W8 (UBOOT_SEL)
UDM0: U1.N20 (DM0), USB_OTG224.D-
UDM1: U1.P20 (DM1), USB_HOST1.2
UDM2: U1.R20 (DM2), USB_HOST2.2
UDP0: U1.N21 (DP0), USB_OTG224.D+
UDP1: U1.P21 (DP1), USB_HOST1.3
UDP2: U1.R21 (DP2), USB_HOST2.3
USB0-IDDET: R55.2, U1.B5 (LCD1_D4/ATAD0/UART4_TX/EINT4/CSI1_D4/PH4), USB_OTG224.ID
USB0-VBUSDET: C135.1, R51.1, R54.2, U1.C5 (LCD1_D5/ATAD1/UART4_RX/EINT5/CSI1_D5/PH5)
USB1-DRV: R58.2, U1.A4 (LCD1_D6/ATAD2/UART5_TX/MS_BS/EINT6/CSI1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), U11.4 (EN)
USB2-DRV: R62.2, U1.A5 (LCD1_D3/ATAIRQ/UART3_CTS/EINT3/CSI1_D3/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), U12.4 (EN)
V+: 1.5V224.1, C1.1, C2.1, C3.2, C4.2, C5.2, C6.2, C7.2, C8.2, C9.2, C10.2, C11.2, C12.2, C19.2, C20.2, C21.2, C22.2, C23.2, C24.2, C25.2, C26.2, C27.2, C28.2, C29.2, C30.2, C31.2, C32.2, C33.2, C34.2, C35.2, C36.2, C47.2, C48.2, C49.2, C50.2, C51.2, C52.2, C53.2, C54.2, C55.2, C56.2, C57.2, C58.2, C59.2, C60.2, C61.2, C62.2, C63.2, C64.2, C201.1, C203.1, C204.1, L14.2, R1.2, R2.2, R6.2, R86.1, U1.G5 (VCC_DRAM), U1.H5 (VCC_DRAM), U1.L5 (VCC_DRAM), U1.M5 (VCC_DRAM), U1.R5 (VCC_DRAM), U1.T5 (VCC_DRAM), U1.W5 (VCC_DRAM), U1.W6 (VCC_DRAM), U1.W7 (VCC_DRAM), U1.Y6 (VCC_DRAM), U2.A1 (VDDQ), U2.A8 (VDDQ), U2.B2 (VDD), U2.C1 (VDDQ), U2.C9 (VDDQ), U2.D2 (VDDQ), U2.D9 (VDD), U2.E9 (VDDQ), U2.F1 (VDDQ), U2.G7 (VDD), U2.H2 (VDDQ), U2.H9 (VDDQ), U2.K2 (VDD), U2.K8 (VDD), U2.N1 (VDD), U2.N9 (VDD), U2.R1 (VDD), U2.R9 (VDD), U3.A1 (VDDQ), U3.A8 (VDDQ), U3.B2 (VDD), U3.C1 (VDDQ), U3.C9 (VDDQ), U3.D2 (VDDQ), U3.D9 (VDD)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

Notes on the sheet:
POWER SUPPLY CIRCUIT
LI-ION_BATTERY
1 x [4Gb DDR3 SDRAM (256Mx16)]
MicroSD
BUTTON
USB-OTG
USB-HOSTs
NAND Flash
32Gb (4096M x 8bit)
GPIO EXTENSION
LCD EXTENSION
EEPROM
MAC Address
16 Kbit
(2048 x 8)
HDMI
SATA
LED
ADC
GIGABIT ETHERNET TRANSCEIVER
We have used a number of fully compatible
but different DDR3 memories due to supply unavailability.
In such cases the memory part name
in the schematic might remain outdated.
It is recommended to always refer to the
exact memory name printed on the component itself.
